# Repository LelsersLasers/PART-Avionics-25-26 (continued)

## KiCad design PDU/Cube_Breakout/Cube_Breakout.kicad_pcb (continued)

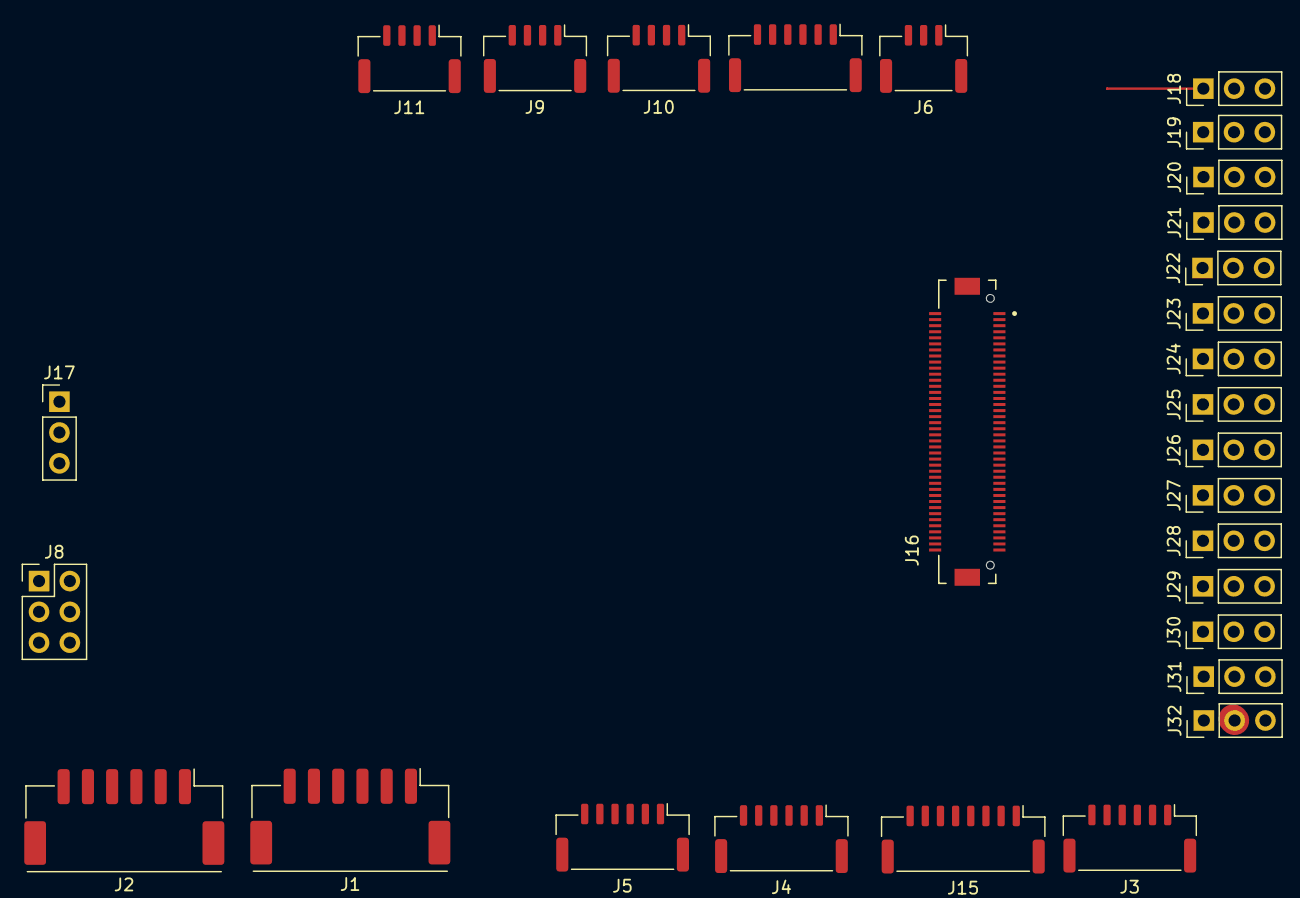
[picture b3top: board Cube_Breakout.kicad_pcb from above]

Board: 2 copper layers, 29 parts (0 on the bottom side), 50 nets.

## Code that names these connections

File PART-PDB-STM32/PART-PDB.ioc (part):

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Mcu.Name=STM32F030F4Px
Mcu.Package=TSSOP20
Mcu.UserName=STM32F030F4Px
PA0.Mode=IN0
PA0.Signal=ADC_IN0
PA1.Mode=IN1
PA1.Signal=ADC_IN1
PA13.Mode=Serial_Wire
PA13.Signal=SYS_SWDIO
PA14.Mode=Serial_Wire
PA14.Signal=SYS_SWCLK
PA2.Mode=Asynchronous
PA2.Signal=USART1_TX
PA3.Mode=Asynchronous
PA3.Signal=USART1_RX
PA4.GPIOParameters=GPIO_Speed,PinState
PA4.GPIO_Speed=GPIO_SPEED_FREQ_HIGH
PA4.PinState=GPIO_PIN_RESET
PA4.Signal=GPIO_Output
PA5.GPIOParameters=GPIO_Speed
PA5.GPIO_Speed=GPIO_SPEED_FREQ_HIGH
PA5.Signal=GPIO_Output
PA6.GPIOParameters=GPIO_Speed
PA6.GPIO_Speed=GPIO_SPEED_FREQ_HIGH
PA6.Signal=GPIO_Output
PA7.GPIOParameters=GPIO_Speed
PA7.GPIO_Speed=GPIO_SPEED_FREQ_HIGH
PA7.Signal=GPIO_Output
PB1.GPIOParameters=GPIO_Speed
PB1.GPIO_Speed=GPIO_SPEED_FREQ_HIGH
PB1.Signal=GPIO_Output
board=custom

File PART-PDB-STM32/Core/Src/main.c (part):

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  current_col = (current_col + 1u) & 0x07u;
}

/* Shift 8 bits into 74AHC595: SER_DATA=PA4, SHIFT_CLK=PA6, MSB first */
static void Matrix_ShiftOut595(uint8_t data)
{
  for (int i = 7; i >= 0; i--)
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  }
}

/* Shift 8 bits into TLC5916: SDI_DATA=PA5, SHIFT_CLK=PA6, MSB first */
static void Matrix_ShiftOut5916(uint8_t data)
{
  for (int i = 7; i >= 0; i--)
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  }
}

/* Pulse OUTPUT_CLOCK (PA7) to latch both shift registers simultaneously */
static void Matrix_Latch(void)
{
  HAL_GPIO_WritePin(GPIOA, GPIO_PIN_7, GPIO_PIN_SET);
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  /*Configure GPIO pin Output Level */
  HAL_GPIO_WritePin(GPIOB, GPIO_PIN_1, GPIO_PIN_RESET);

  /*Configure GPIO pins : PA4 PA5 PA6 PA7 */
  GPIO_InitStruct.Pin = GPIO_PIN_4|GPIO_PIN_5|GPIO_PIN_6|GPIO_PIN_7;
  GPIO_InitStruct.Mode = GPIO_MODE_OUTPUT_PP;
  GPIO_InitStruct.Pull = GPIO_NOPULL;
  GPIO_InitStruct.Speed = GPIO_SPEED_FREQ_HIGH;
  HAL_GPIO_Init(GPIOA, &GPIO_InitStruct);

  /*Configure GPIO pin : PB1 */
  GPIO_InitStruct.Pin = GPIO_PIN_1;
  GPIO_InitStruct.Mode = GPIO_MODE_OUTPUT_PP;
  GPIO_InitStruct.Pull = GPIO_NOPULL;
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
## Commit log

2025-10-15 Added the input connectors/Added buck converter/Wired the future buck booster
    Added the input connectors/Added buck converter from 7-40V to 5V and 2A and wired the future buck booster.
2025-10-15 Added some ports, started labeling
    DF17 port, see notes page for more port details
2025-10-19 Updated Breakout with different ports and added more labels
    I updated some of the ports with what is actually on the top of the board. I added labels for most of the top ports. Still need to do side ports
2025-10-20 Finished Voltage Sensing Circuit based on INA219 chips
2025-10-20 Added more labels and ports
    Added servo ports and labeled them. Labeled power ports
2025-10-21 Changed font color
    Small change
2025-10-22 Changed from Battery Cells to Battery Packs
2025-10-22 Schematics Servo Pin Change and PCB design Started
    Changed servo pins to 3 1x15 connectors to 15 1x3 connectors. Added some more footprints. Started laying out the pcb
2025-10-25 Added footprints for all components
    No footprint for relay yet
2025-10-27 Added LM51450 symbol
2025-10-27 Added buck converter
2025-10-27 Copied over files for undervoltage protection
2025-10-27 Added overcurrent protection with op-amps and comparators
2025-11-04 Revise README for PART Avionics 2025-2026
    Updated project title and added details about KiCad projects and embedded code.
2025-11-05 Tyler Palino - Adding the most updated PCB file
2025-11-11 Fixed XT-90 connector to male
2025-11-11 Assign footprints
2025-11-11 11/10 basic pcb build (pre-route)
2025-11-11 updated pcb, pre-route w/o stm32 (11/10)
2025-11-11 11/11 basic pcb build w/ stm32
2025-11-12 Added 5v ->3.3v LDO
2025-11-13 LED status for rails and GPIO
2025-11-13 LDO (thanks @Kade-Zisko)
2025-11-13 UART
2025-11-13 Fix schematic title
2025-11-13 Mounting holes
2025-11-13 LED matrix control components
2025-11-13 chore: Macos gitignore
2025-11-13 feat: PSM info + refactor beginnings
2025-11-13 links to kicanvas viewer (Altium 365 but for Kicad)
2025-11-13 PDU: ST-Link out
2025-11-13 Fix sense out connector
    WHY does it need a 5v out??
2025-11-13 Footprint: LED matrix component
2025-11-13 Trying to write the led matrix
2025-11-13 Moving WIP led matrix to sub schematic
2025-11-13 Mostly wiring + side of LED matrix
2025-11-13 Connecting LED -> SINK
2025-11-13 local -> global labels?
2025-11-13 Wiring SINK + maybe fixing control clocks
2025-11-13 updating resistor value
2025-11-14 feat: DIP footprints for SRs
2025-11-15 feat: Servo battery csense + filtering
2025-11-15 feat: Port beginnings
2025-11-15 Summarization of schematic on ROOT 2
2025-11-15 feat: 80pin with holes from altium
2025-11-15 Add connectors
2025-11-15 feat: Schem done
2025-11-15 feat: Symbol cleanup
2025-11-15 Manufacturing properties
2025-11-15 feat: Rest of part nos
2025-11-15 Fix resistor/capactor values and MPs
2025-11-15 Started component placement
2025-11-15 Initial layout
2025-11-15 XT60 purchase link
2025-11-15 12v buck (5v buck but with R1 sized for 12v)
2025-11-15 5v output
2025-11-15 feat: Buck fixup + new footprints
2025-11-16 12v LED indicator
2025-11-17 feat: 12V buck + real footprints
2025-11-17 Fix rules checker (partial)
2025-11-18 Add missing no connect from ERC error
2025-11-18 Committed some Electrical Rules Checker Warnings
2025-11-18 feat; pdb routing start
2025-11-18 Mid route
2025-11-18 feat: Start part no.s for PDB
2025-11-18 routing somewhat connected
2025-11-19 (11/18/25) Fixes
    - Fixed overlapping wiring
    - Fixed incomplete connection/floating NCs
    - TODO: Update footprints (changed pin on buck boost)
    - TODO: Fix LTC3114 (24V buck boost) wiring (U4 Pin 3 and PWR_FLAG)
    - Decouple +24V? Use: https://www.analog.com/en/products/ltc3114-1.html
    - TODO: Fix redundant grounding
2025-11-19 feat; pdb routing start
    # Conflicts:
    # PDB/pdb.kicad_sch
2025-11-19 feat: Post-merge cleanup + pcb update
2025-11-19 Smaller pcb
2025-11-20 ERC Rules Fixes
2025-11-20 Feat: routing works with new schematic
2025-11-20 feat: BOM items from meeting
2025-11-20 feat: Update some footprints
2025-11-20 feat: Update switch footprint
2025-11-21 Feat: Add planes, remove fuse, et cetera
2025-11-21 feat: Switch to gh for analog
2025-11-21 feat: PDB big routing time
2025-11-22 feat: Rough draft of PDB routing
2025-11-30 More routing progress
2025-12-01 Most updated PCB (I will work on it more tomorrow morning)
2025-12-01 fix: Silkscreen cleanup + minor improvements
2025-12-02 PDB now passes DRC
    Sorta.... bunch of things with U1 ignored (Weird stuff came with footprint)
2025-12-02 Fixed resistor part numbers
2025-12-02 Feat: assign BJT part numbers, remove DNPs for screenshots
2025-12-02 Jetson and Rocket output are XT30-F instead of 2 pin socket thing
2025-12-02 Final Changes - Pre CDR
    12/2/2025
2025-12-02 feat: XT30s + some prettying
2026-01-05 feat: Final gerber changes
2026-01-05 fix: Power traces
2026-01-05 fix: some carrier part nums
2026-01-06 feat: Carrier buck + packed outputs
2026-01-06 feat: Carrier done
2026-01-07 feat: Final silkscreens + sideways pdb
2026-01-09 Prettying + Resolve ERC
2026-01-12 Typo in silkscreen
2026-01-21 New blank STM32F030F4P6 project
2026-01-28 *.ioc for STM32
    Also fixed some silkscreen typos on PDB
2026-03-25 Fix resistor values to accurately reflect Prod PCB
    The original resistor values for the onboard battery voltage monitor voltage divider were calculated wrong. In order to fix this without the need for new parts, we flipped the two resistors.
2026-03-25 STM32 Setup
    * PDB Logger Script (writes detailed results to CSV)
    * IOC (configs migrated, updated baud rate, GPIO out speed)
    * General voltage/current sensing
    this took a while bc the last time i opened cubeide was before they required you to login and also before they made u do the ioc separate to the project/firmware
2026-04-06 R&D's config
2026-04-06 Fix folder name
2026-04-06 Copying the R&D one for now
2026-04-07 Copy of the 4/6/26 ArduPilot params from R&D
2026-04-07 Pulling config off of black comp cube
2026-04-08 Adding a diff for easier viewing
2026-04-09 4/8: Adjust airspeed, orientation, right aileron setup, some RTL
2026-04-09 Radio calibration
2026-04-09 X frame, rudder, left aileron
2026-04-23 4/22/26 Nemo params
2026-04-23 Remove old files
2026-04-23 Rename
